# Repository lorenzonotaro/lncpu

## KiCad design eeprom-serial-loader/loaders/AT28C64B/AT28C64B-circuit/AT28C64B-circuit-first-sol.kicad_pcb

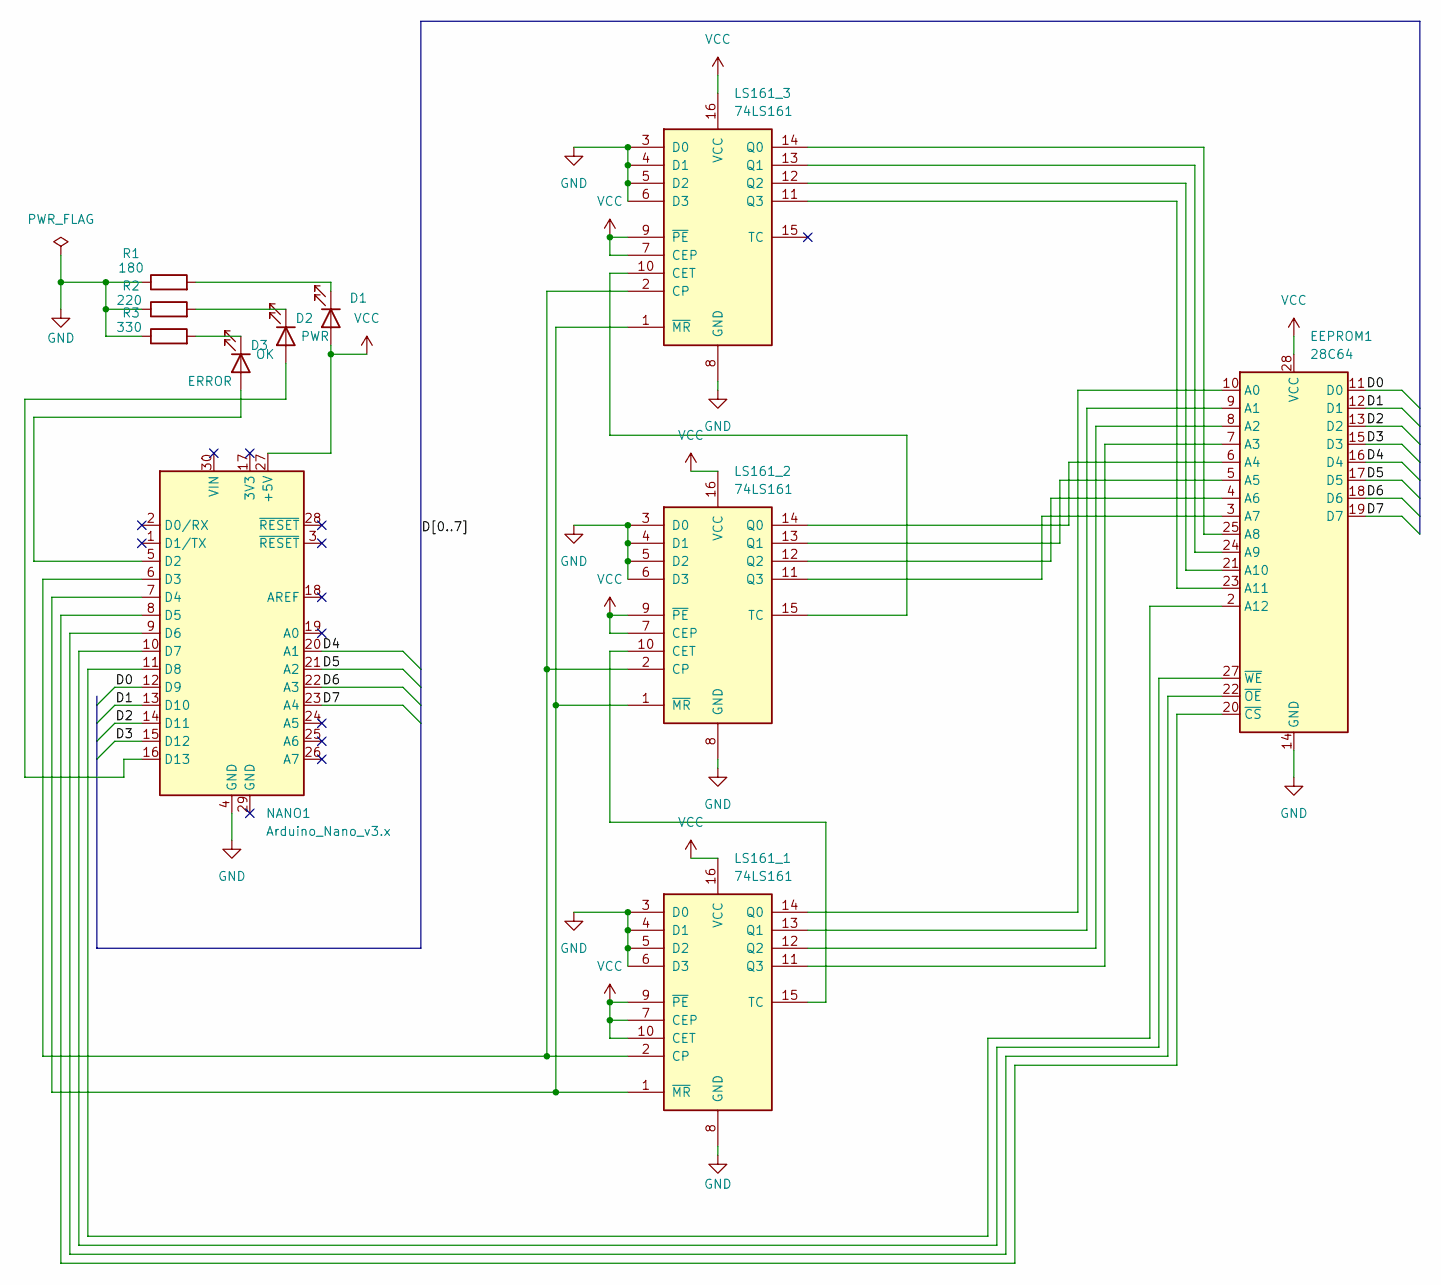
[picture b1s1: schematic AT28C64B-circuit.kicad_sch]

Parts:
D1: PWR; LED_D3.0mm
D2: OK; LED_D3.0mm
D3: ERROR; LED_D3.0mm
EEPROM1: 28C64; DIP-28_W15.24mm_Socket_LongPads
LS161_1, LS161_2, LS161_3: 74LS161; DIP-16_W7.62mm
NANO1: Arduino_Nano_v3.x; Arduino_Nano
R1: 180; R_Axial_DIN0207_L6.3mm_D2.5mm_P10.16mm_Horizontal
R2: 220; R_Axial_DIN0207_L6.3mm_D2.5mm_P10.16mm_Horizontal
R3: 330; R_Axial_DIN0207_L6.3mm_D2.5mm_P10.16mm_Horizontal

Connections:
/D0: EEPROM1.11 (D0), NANO1.12 (D9)
/D1: EEPROM1.12 (D1), NANO1.13 (D10)
/D2: EEPROM1.13 (D2), NANO1.14 (D11)
/D3: EEPROM1.15 (D3), NANO1.15 (D12)
/D4: EEPROM1.16 (D4), NANO1.20 (A1)
/D5: EEPROM1.17 (D5), NANO1.21 (A2)
/D6: EEPROM1.18 (D6), NANO1.22 (A3)
/D7: EEPROM1.19 (D7), NANO1.23 (A4)
GND: EEPROM1.14 (GND), LS161_1.3 (D0), LS161_1.4 (D1), LS161_1.5 (D2), LS161_1.6 (D3), LS161_1.8 (GND), LS161_2.3 (D0), LS161_2.4 (D1), LS161_2.5 (D2), LS161_2.6 (D3), LS161_2.8 (GND), LS161_3.3 (D0), LS161_3.4 (D1), LS161_3.5 (D2), LS161_3.6 (D3), LS161_3.8 (GND), NANO1.4 (GND), R1.1, R2.1, R3.1
unnamed: D1.1 (K), R1.2
unnamed: D2.2 (A), NANO1.16 (D13)
unnamed: D2.1 (K), R2.2
unnamed: D3.2 (A), NANO1.5 (D2)
unnamed: D3.1 (K), R3.2
unnamed: EEPROM1.10 (A0), LS161_1.14 (Q0)
unnamed: EEPROM1.9 (A1), LS161_1.13 (Q1)
unnamed: EEPROM1.8 (A2), LS161_1.12 (Q2)
unnamed: EEPROM1.7 (A3), LS161_1.11 (Q3)
unnamed: EEPROM1.6 (A4), LS161_2.14 (Q0)
unnamed: EEPROM1.5 (A5), LS161_2.13 (Q1)
unnamed: EEPROM1.4 (A6), LS161_2.12 (Q2)
unnamed: EEPROM1.3 (A7), LS161_2.11 (Q3)
unnamed: EEPROM1.25 (A8), LS161_3.14 (Q0)
unnamed: EEPROM1.24 (A9), LS161_3.13 (Q1)
unnamed: EEPROM1.21 (A10), LS161_3.12 (Q2)
unnamed: EEPROM1.23 (A11), LS161_3.11 (Q3)
unnamed: EEPROM1.2 (A12), NANO1.11 (D8)
unnamed: EEPROM1.20 (~CS), NANO1.8 (D5)
unnamed: EEPROM1.22 (~OE), NANO1.9 (D6)
unnamed: EEPROM1.27 (~WE), NANO1.10 (D7)
unnamed: LS161_1.2 (CP), LS161_2.2 (CP), LS161_3.2 (CP), NANO1.6 (D3)
unnamed: LS161_1.15 (TC), LS161_2.10 (CET)
unnamed: LS161_1.1 (~MR), LS161_2.1 (~MR), LS161_3.1 (~MR), NANO1.7 (D4)
unnamed: LS161_2.15 (TC), LS161_3.10 (CET)
VCC: D1.2 (A), EEPROM1.28 (VCC), LS161_1.7 (CEP), LS161_1.9 (~PE), LS161_1.10 (CET), LS161_1.16 (VCC), LS161_2.7 (CEP), LS161_2.9 (~PE), LS161_2.16 (VCC), LS161_3.7 (CEP), LS161_3.9 (~PE), LS161_3.16 (VCC), NANO1.27 (+5V)

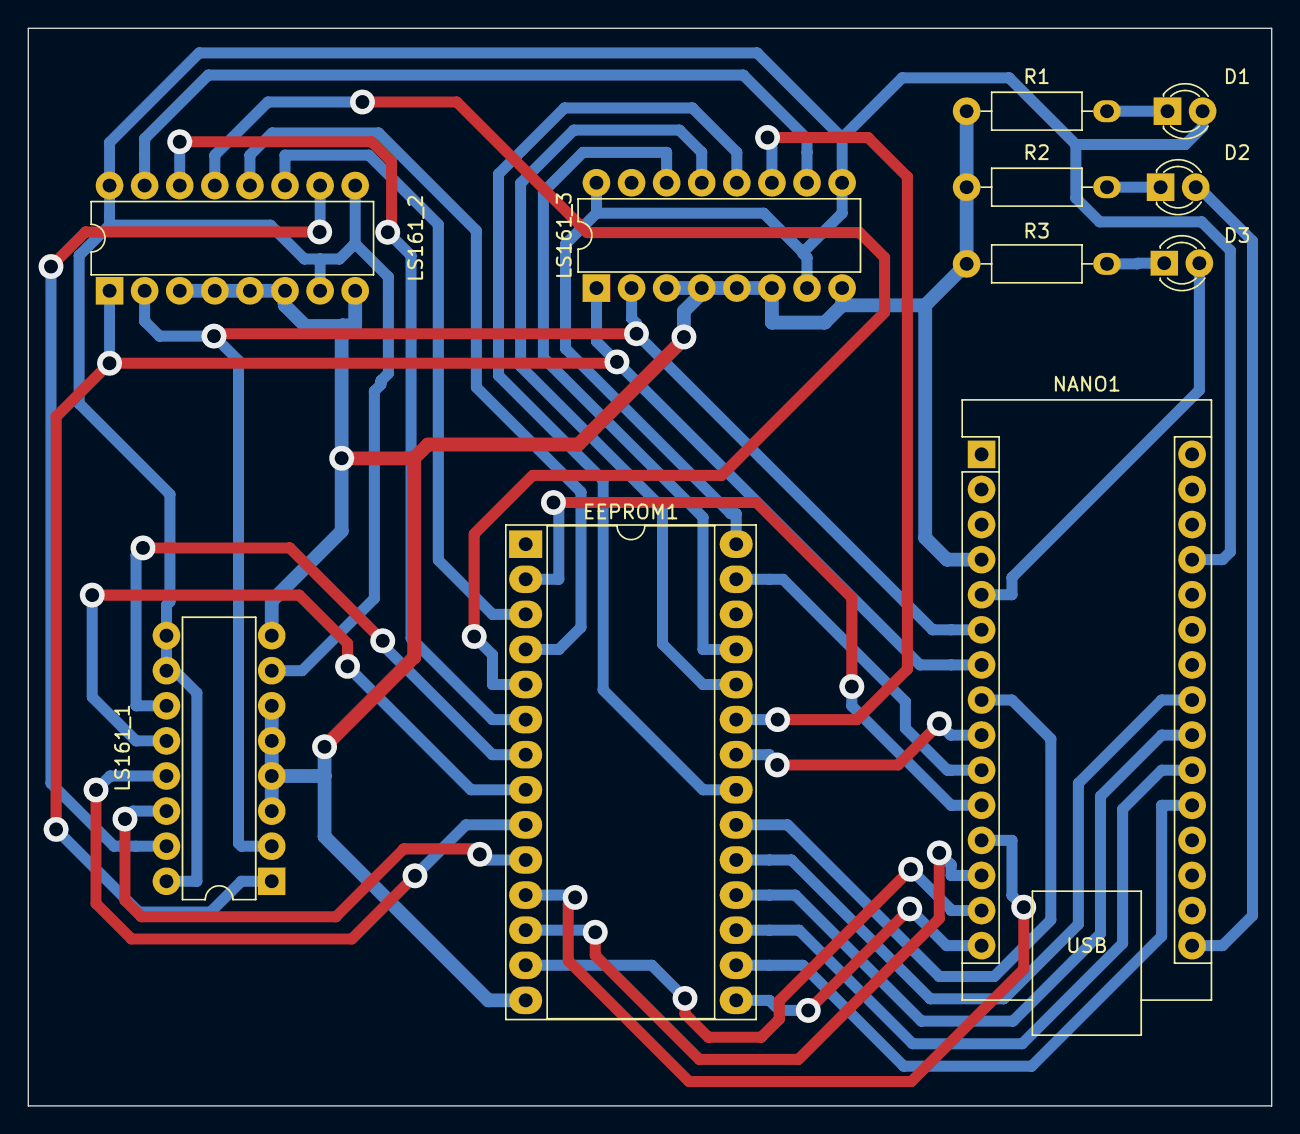
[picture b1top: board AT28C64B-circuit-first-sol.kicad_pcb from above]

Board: 2 copper layers, 90.0 x 78.0 mm, 11 parts (0 on the bottom side), 35 nets.

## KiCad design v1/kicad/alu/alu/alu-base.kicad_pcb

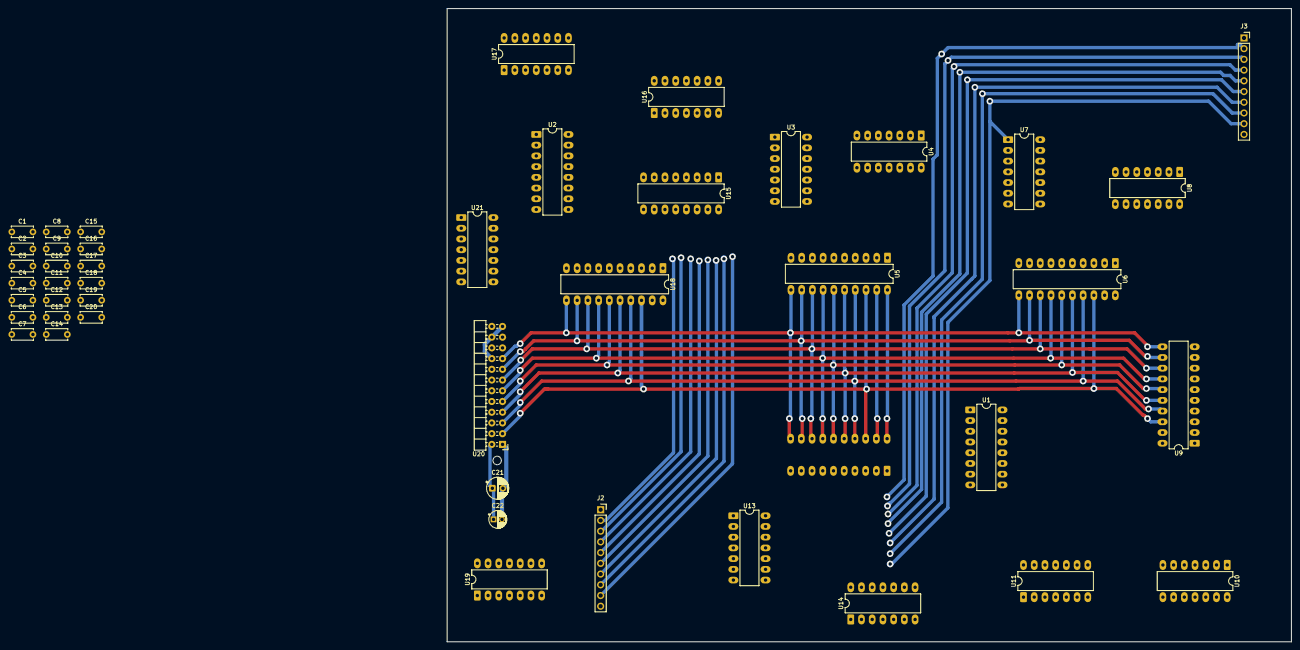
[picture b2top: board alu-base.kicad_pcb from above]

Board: 2 copper layers, 200.0 x 150.0 mm, 45 parts (1 on the bottom side), 92 nets.

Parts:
C1, C2, C3, C4, C5, C6, C7, C8, C9, C10, C11, C12, C13, C14, C15: 100n; C_Disc_D5.0mm_W2.5mm_P5.00mm
C16, C17, C18, C19, C20: 220n; C_Disc_D5.0mm_W2.5mm_P5.00mm
C21: 47uF; CP_Radial_D5.0mm_P2.50mm
C22: 1uF; CP_Radial_D4.0mm_P2.00mm-Large-Holes
J2: X_{in}; PinSocket_1x10_P2.54mm_Vertical
J3: Y_{in}; PinSocket_1x10_P2.54mm_Vertical
U1: 74LS138; DIP-16_W7.62mm_LongPads
U2, U15: 74LS283; DIP-16_W7.62mm_LongPads
U3, U4: 74LS32; DIP-14_W7.62mm_LongPads
U5, U6, U9, U12, U18: 74HCT541; DIP-20_W7.62mm_LongPads
U7, U8, U19: 74LS08; DIP-14_W7.62mm_LongPads
U10, U11, U16, U17, U21: 74LS86; DIP-14_W7.62mm_LongPads
U13, U14: 74LS04; DIP-14_W7.62mm_LongPads
U20: LNCPU Type B Header; LNCPU_Type_B_Header

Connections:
/D0: U5.18 (Y0), U6.18 (Y0), U9.18 (Y0), U12.18 (Y0), U18.18 (Y0), U20.3 (DBUS_{0})
/D1: U5.17 (Y1), U6.17 (Y1), U9.17 (Y1), U12.17 (Y1), U18.17 (Y1), U20.5 (DBUS_{1})
/D2: U5.16 (Y2), U6.16 (Y2), U9.16 (Y2), U12.16 (Y2), U18.16 (Y2), U20.7 (DBUS_{2})
/D3: U5.15 (Y3), U6.15 (Y3), U9.15 (Y3), U12.15 (Y3), U18.15 (Y3), U20.9 (DBUS_{3})
/D4: U5.14 (Y4), U6.14 (Y4), U9.14 (Y4), U12.14 (Y4), U18.14 (Y4), U20.11 (DBUS_{4})
/D5: U5.13 (Y5), U6.13 (Y5), U9.13 (Y5), U12.13 (Y5), U18.13 (Y5), U20.13 (DBUS_{5})
/D6: U5.12 (Y6), U6.12 (Y6), U9.12 (Y6), U12.12 (Y6), U18.12 (Y6), U20.15 (DBUS_{6})
/D7: U5.11 (Y7), U6.11 (Y7), U9.11 (Y7), U12.11 (Y7), U18.11 (Y7), U20.17 (DBUS_{7})
/X0: J2.2 (D0), U4.13, U8.13, U11.13, U14.3, U15.5 (A1)
/X1: J2.3 (D1), U3.13, U7.13, U10.13, U14.1, U15.3 (A2)
/X2: J2.4 (D2), U4.10, U8.10, U11.10, U13.13, U15.14 (A3)
/X3: J2.5 (D3), U3.10, U7.10, U10.10, U13.11, U15.12 (A4)
/X4: J2.6 (D4), U2.5 (A1), U4.5, U8.5, U11.5, U13.9
/X5: J2.7 (D5), U2.3 (A2), U3.5, U7.5, U10.5, U13.5
/X6: J2.8 (D6), U2.14 (A3), U4.2, U8.2, U11.2, U13.3
/X7: J2.9 (D7), U2.12 (A4), U3.2, U7.2, U10.2, U13.1
/Y0: J3.2 (D0), U4.12, U8.12, U11.12, U17.13
/Y1: J3.3 (D1), U3.12, U7.12, U10.12, U16.13
/Y2: J3.4 (D2), U4.9, U8.9, U11.9, U17.10
/Y3: J3.5 (D3), U3.9, U7.9, U10.9, U16.10
/Y4: J3.6 (D4), U4.4, U8.4, U11.4, U17.5
/Y5: J3.7 (D5), U3.4, U7.4, U10.4, U16.5
/Y6: J3.8 (D6), U4.1, U8.1, U11.1, U17.2
/Y7: J3.9 (D7), U3.1, U7.1, U10.1, U16.2
/Y_{xor}EN2_{0}: U15.6 (B1), U17.11
/Y_{xor}EN2_{1}: U15.2 (B2), U16.11
/Y_{xor}EN2_{2}: U15.15 (B3), U17.8
/Y_{xor}EN2_{3}: U15.11 (B4), U16.8
/Y_{xor}EN2_{4}: U2.6 (B1), U17.6
/Y_{xor}EN2_{5}: U2.2 (B2), U16.6
/Y_{xor}EN2_{6}: U2.15 (B3), U17.3
/Y_{xor}EN2_{7}: U2.11 (B4), U16.3
/~EN1: U1.14 (O1), U19.5
/~EN2: U1.13 (O2), U14.5, U19.4
/~EN3: U1.12 (O3), U5.1 (G1)
/~EN4: U1.11 (O4), U6.1 (G1)
/~EN5: U1.10 (O5), U9.1 (G1)
/~EN6: U1.9 (O6), U12.1 (G1)
C_{out}: U19.3, U20.14 (CTRL_{5})
GND: C1.2, C2.1, C3.1, C4.1, C5.1, C6.1, C7.1, C8.1, C9.1, C10.1, C11.1, C12.1, C13.1, C14.2, C15.2, C16.2, C17.2, C18.2, C19.2, C20.2, C21.2, C22.2, J2.1 (GND), J2.10 (GND), J3.1 (GND), J3.10 (GND), U1.8 (GND), U2.8 (GND), U3.7 (GND), U4.7 (GND), U5.10 (GND), U6.10 (GND), U7.7 (GND), U8.7 (GND), U9.10 (GND), U10.7 (GND), U11.7 (GND), U12.10 (GND), U13.7 (GND), U14.7 (GND), U14.11, U14.13, U15.8 (GND), U16.7 (GND), U17.7 (GND), U18.10 (GND), U19.7 (GND), U19.9, U19.10, U19.12, U19.13, U20.1 (GND), U20.18 (GND), U20.22 (GND), U20.23 (GND), U21.4, U21.5, U21.7 (GND), U21.9, U21.10, U21.12, U21.13
unnamed: U1.1 (A0), U20.12 (CTRL_{4})
unnamed: U1.2 (A1), U20.10 (CTRL_{3})
unnamed: U1.3 (A2), U20.8 (CTRL_{2})
unnamed: U1.4 (E1), U20.4 (CTRL_{0})
unnamed: U2.9 (C4), U21.2
unnamed: U4.11, U5.2 (A0)
unnamed: U3.11, U5.3 (A1)
unnamed: U4.8, U5.4 (A2)
unnamed: U3.8, U5.5 (A3)
unnamed: U4.6, U5.6 (A4)
unnamed: U3.6, U5.7 (A5)
unnamed: U4.3, U5.8 (A6)
unnamed: U3.3, U5.9 (A7)
unnamed: U6.2 (A0), U8.11
unnamed: U6.3 (A1), U7.11
unnamed: U6.4 (A2), U8.8
unnamed: U6.5 (A3), U7.8
unnamed: U6.6 (A4), U8.6
unnamed: U6.7 (A5), U7.6
unnamed: U6.8 (A6), U8.3
unnamed: U6.9 (A7), U7.3
unnamed: U9.2 (A0), U11.11
unnamed: U9.3 (A1), U10.11
unnamed: U9.4 (A2), U11.8
unnamed: U9.5 (A3), U10.8
unnamed: U9.6 (A4), U11.6
unnamed: U9.7 (A5), U10.6
unnamed: U9.8 (A6), U11.3
unnamed: U9.9 (A7), U10.3
unnamed: U12.2 (A0), U14.4
unnamed: U12.3 (A1), U14.2
unnamed: U12.4 (A2), U13.12
unnamed: U12.5 (A3), U13.10
unnamed: U12.6 (A4), U13.8
unnamed: U12.7 (A5), U13.6
unnamed: U12.8 (A6), U13.4
unnamed: U12.9 (A7), U13.2
unnamed: U14.8, U19.2
unnamed: U14.6, U15.7 (C0), U16.1, U16.4, U16.9, U16.12, U17.1, U17.4, U17.9, U17.12, U21.1
unnamed: U2.7 (C0), U15.9 (C4)
unnamed: U15.4 (S1), U18.2 (A0)
unnamed: U15.1 (S2), U18.3 (A1)
unnamed: U15.13 (S3), U18.4 (A2)
unnamed: U15.10 (S4), U18.5 (A3)
unnamed: U2.4 (S1), U18.6 (A4)
unnamed: U2.1 (S2), U18.7 (A5)
unnamed: U2.13 (S3), U18.8 (A6)
unnamed: U2.10 (S4), U18.9 (A7)
unnamed: U14.9, U18.1 (G1), U19.6
unnamed: U19.1, U21.3
VCC: C1.1, C2.2, C3.2, C4.2, C5.2, C6.2, C7.2, C8.2, C9.2, C10.2, C11.2, C12.2, C13.2, C14.1, C15.1, C16.1, C17.1, C18.1, C19.1, C20.1, C21.1, C22.1, U1.6 (E3), U1.16 (VCC), U2.16 (VCC), U3.14 (VCC), U4.14 (VCC), U5.20 (VCC), U6.20 (VCC), U7.14 (VCC), U8.14 (VCC), U9.20 (VCC), U10.14 (VCC), U11.14 (VCC), U12.20 (VCC), U13.14 (VCC), U14.14 (VCC), U15.16 (VCC), U16.14 (VCC), U17.14 (VCC), U18.20 (VCC), U19.14 (VCC), U20.2 (VCC), U20.24 (VCC), U21.14 (VCC)
~ALU_{out}: U1.5 (E2), U5.19 (G2), U6.19 (G2), U9.19 (G2), U12.19 (G2), U18.19 (G2), U20.6 (CTRL_{1})

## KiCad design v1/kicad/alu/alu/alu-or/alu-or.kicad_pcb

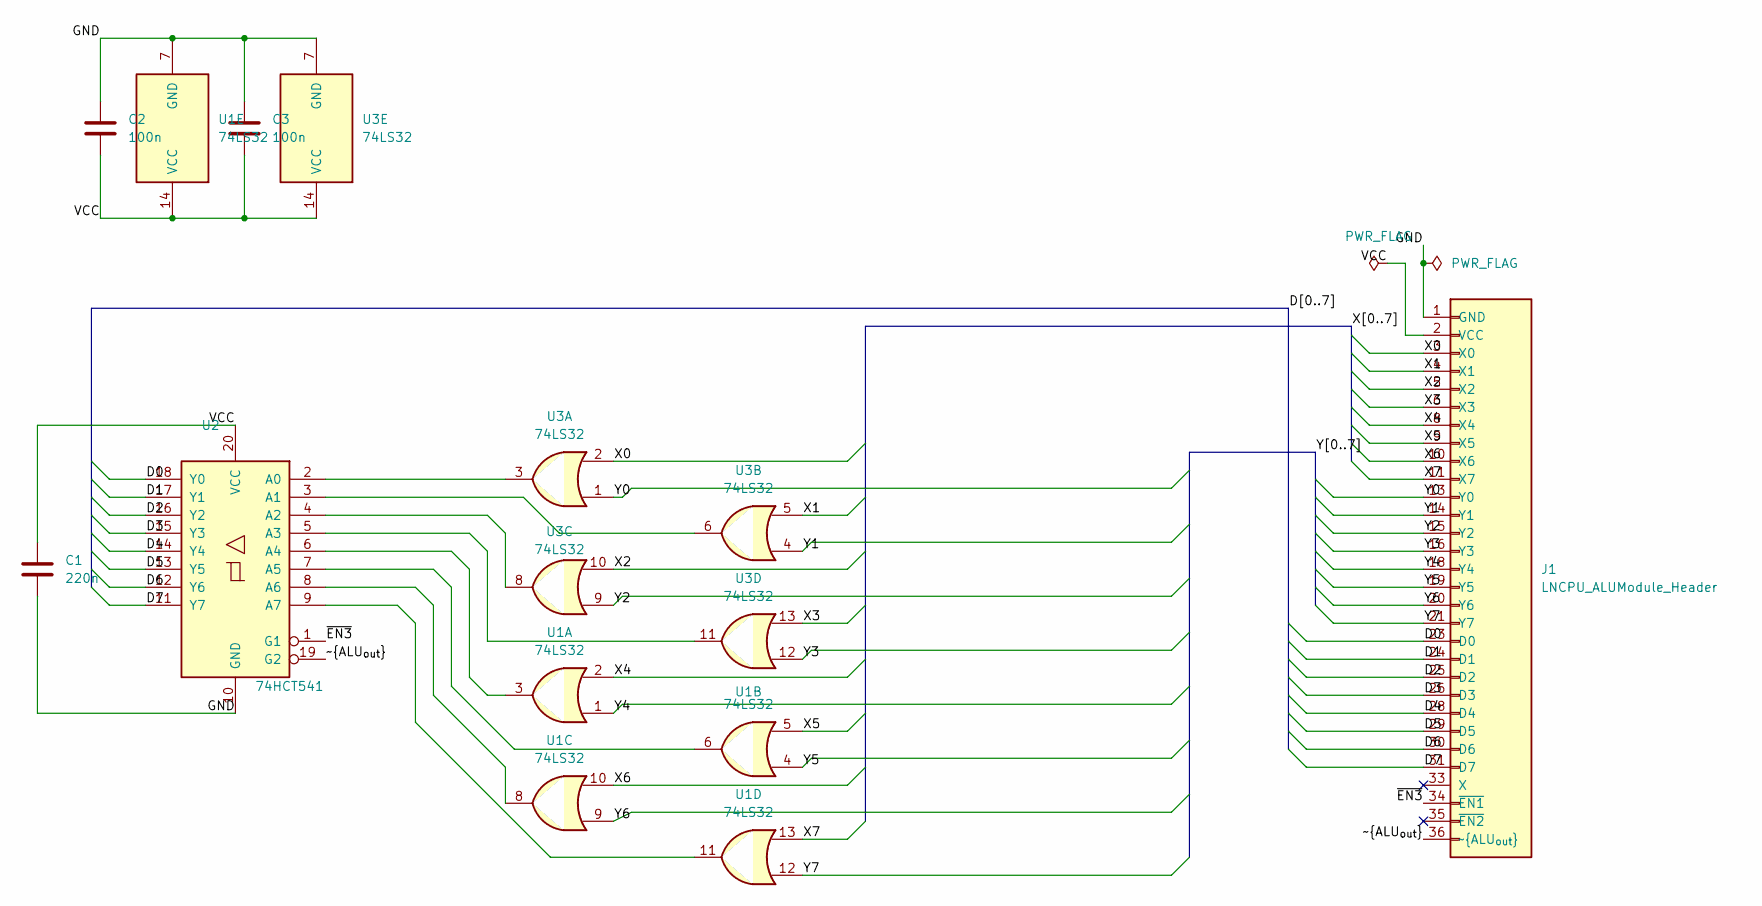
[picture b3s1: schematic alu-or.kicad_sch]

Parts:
C1: 220n; C_Disc_D5.0mm_W2.5mm_P5.00mm
C2, C3: 100n; C_Disc_D5.0mm_W2.5mm_P5.00mm
J1: LNCPU_ALUModule_Header; LNCPU_ALU_Module_Header
U1, U3: 74LS32; DIP-14_W7.62mm_LongPads
U2: 74HCT541; DIP-20_W7.62mm_LongPads

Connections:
/D0: J1.23 (D0), U2.18 (Y0)
/D1: J1.24 (D1), U2.17 (Y1)
/D2: J1.25 (D2), U2.16 (Y2)
/D3: J1.26 (D3), U2.15 (Y3)
/D4: J1.28 (D4), U2.14 (Y4)
/D5: J1.29 (D5), U2.13 (Y5)
/D6: J1.30 (D6), U2.12 (Y6)
/D7: J1.31 (D7), U2.11 (Y7)
/GND: C1.2, C2.1, C3.1, J1.1 (GND), J1.7 (GND), J1.12 (GND), J1.17 (GND), J1.22 (GND), J1.27 (GND), J1.32 (GND), J1.37 (GND), U1.7 (GND), U2.10 (GND), U3.7 (GND)
/VCC: C1.1, C2.2, C3.2, J1.2 (VCC), J1.38 (VCC), U1.14 (VCC), U2.20 (VCC), U3.14 (VCC)
/X0: J1.3 (X0), U3.2
/X1: J1.4 (X1), U3.5
/X2: J1.5 (X2), U3.10
/X3: J1.6 (X3), U3.13
/X4: J1.8 (X4), U1.2
/X5: J1.9 (X5), U1.5
/X6: J1.10 (X6), U1.10
/X7: J1.11 (X7), U1.13
/Y0: J1.13 (Y0), U3.1
/Y1: J1.14 (Y1), U3.4
/Y2: J1.15 (Y2), U3.9
/Y3: J1.16 (Y3), U3.12
/Y4: J1.18 (Y4), U1.1
/Y5: J1.19 (Y5), U1.4
/Y6: J1.20 (Y6), U1.9
/Y7: J1.21 (Y7), U1.12
/~ALU_{out}: J1.36 (~ALU_{out}), U2.19 (G2)
/~EN3: J1.34 (~EN1), U2.1 (G1)
unnamed: U2.2 (A0), U3.3
unnamed: U2.3 (A1), U3.6
unnamed: U2.4 (A2), U3.8
unnamed: U2.5 (A3), U3.11
unnamed: U1.3, U2.6 (A4)
unnamed: U1.6, U2.7 (A5)
unnamed: U1.8, U2.8 (A6)
unnamed: U1.11, U2.9 (A7)

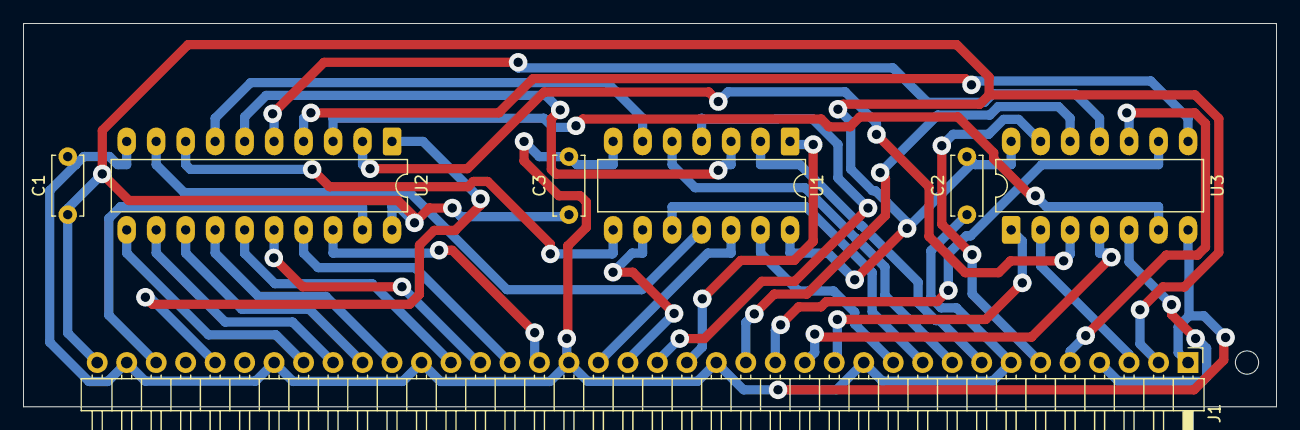
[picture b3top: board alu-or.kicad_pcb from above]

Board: 2 copper layers, 107.9 x 33.0 mm, 7 parts (0 on the bottom side), 36 nets.

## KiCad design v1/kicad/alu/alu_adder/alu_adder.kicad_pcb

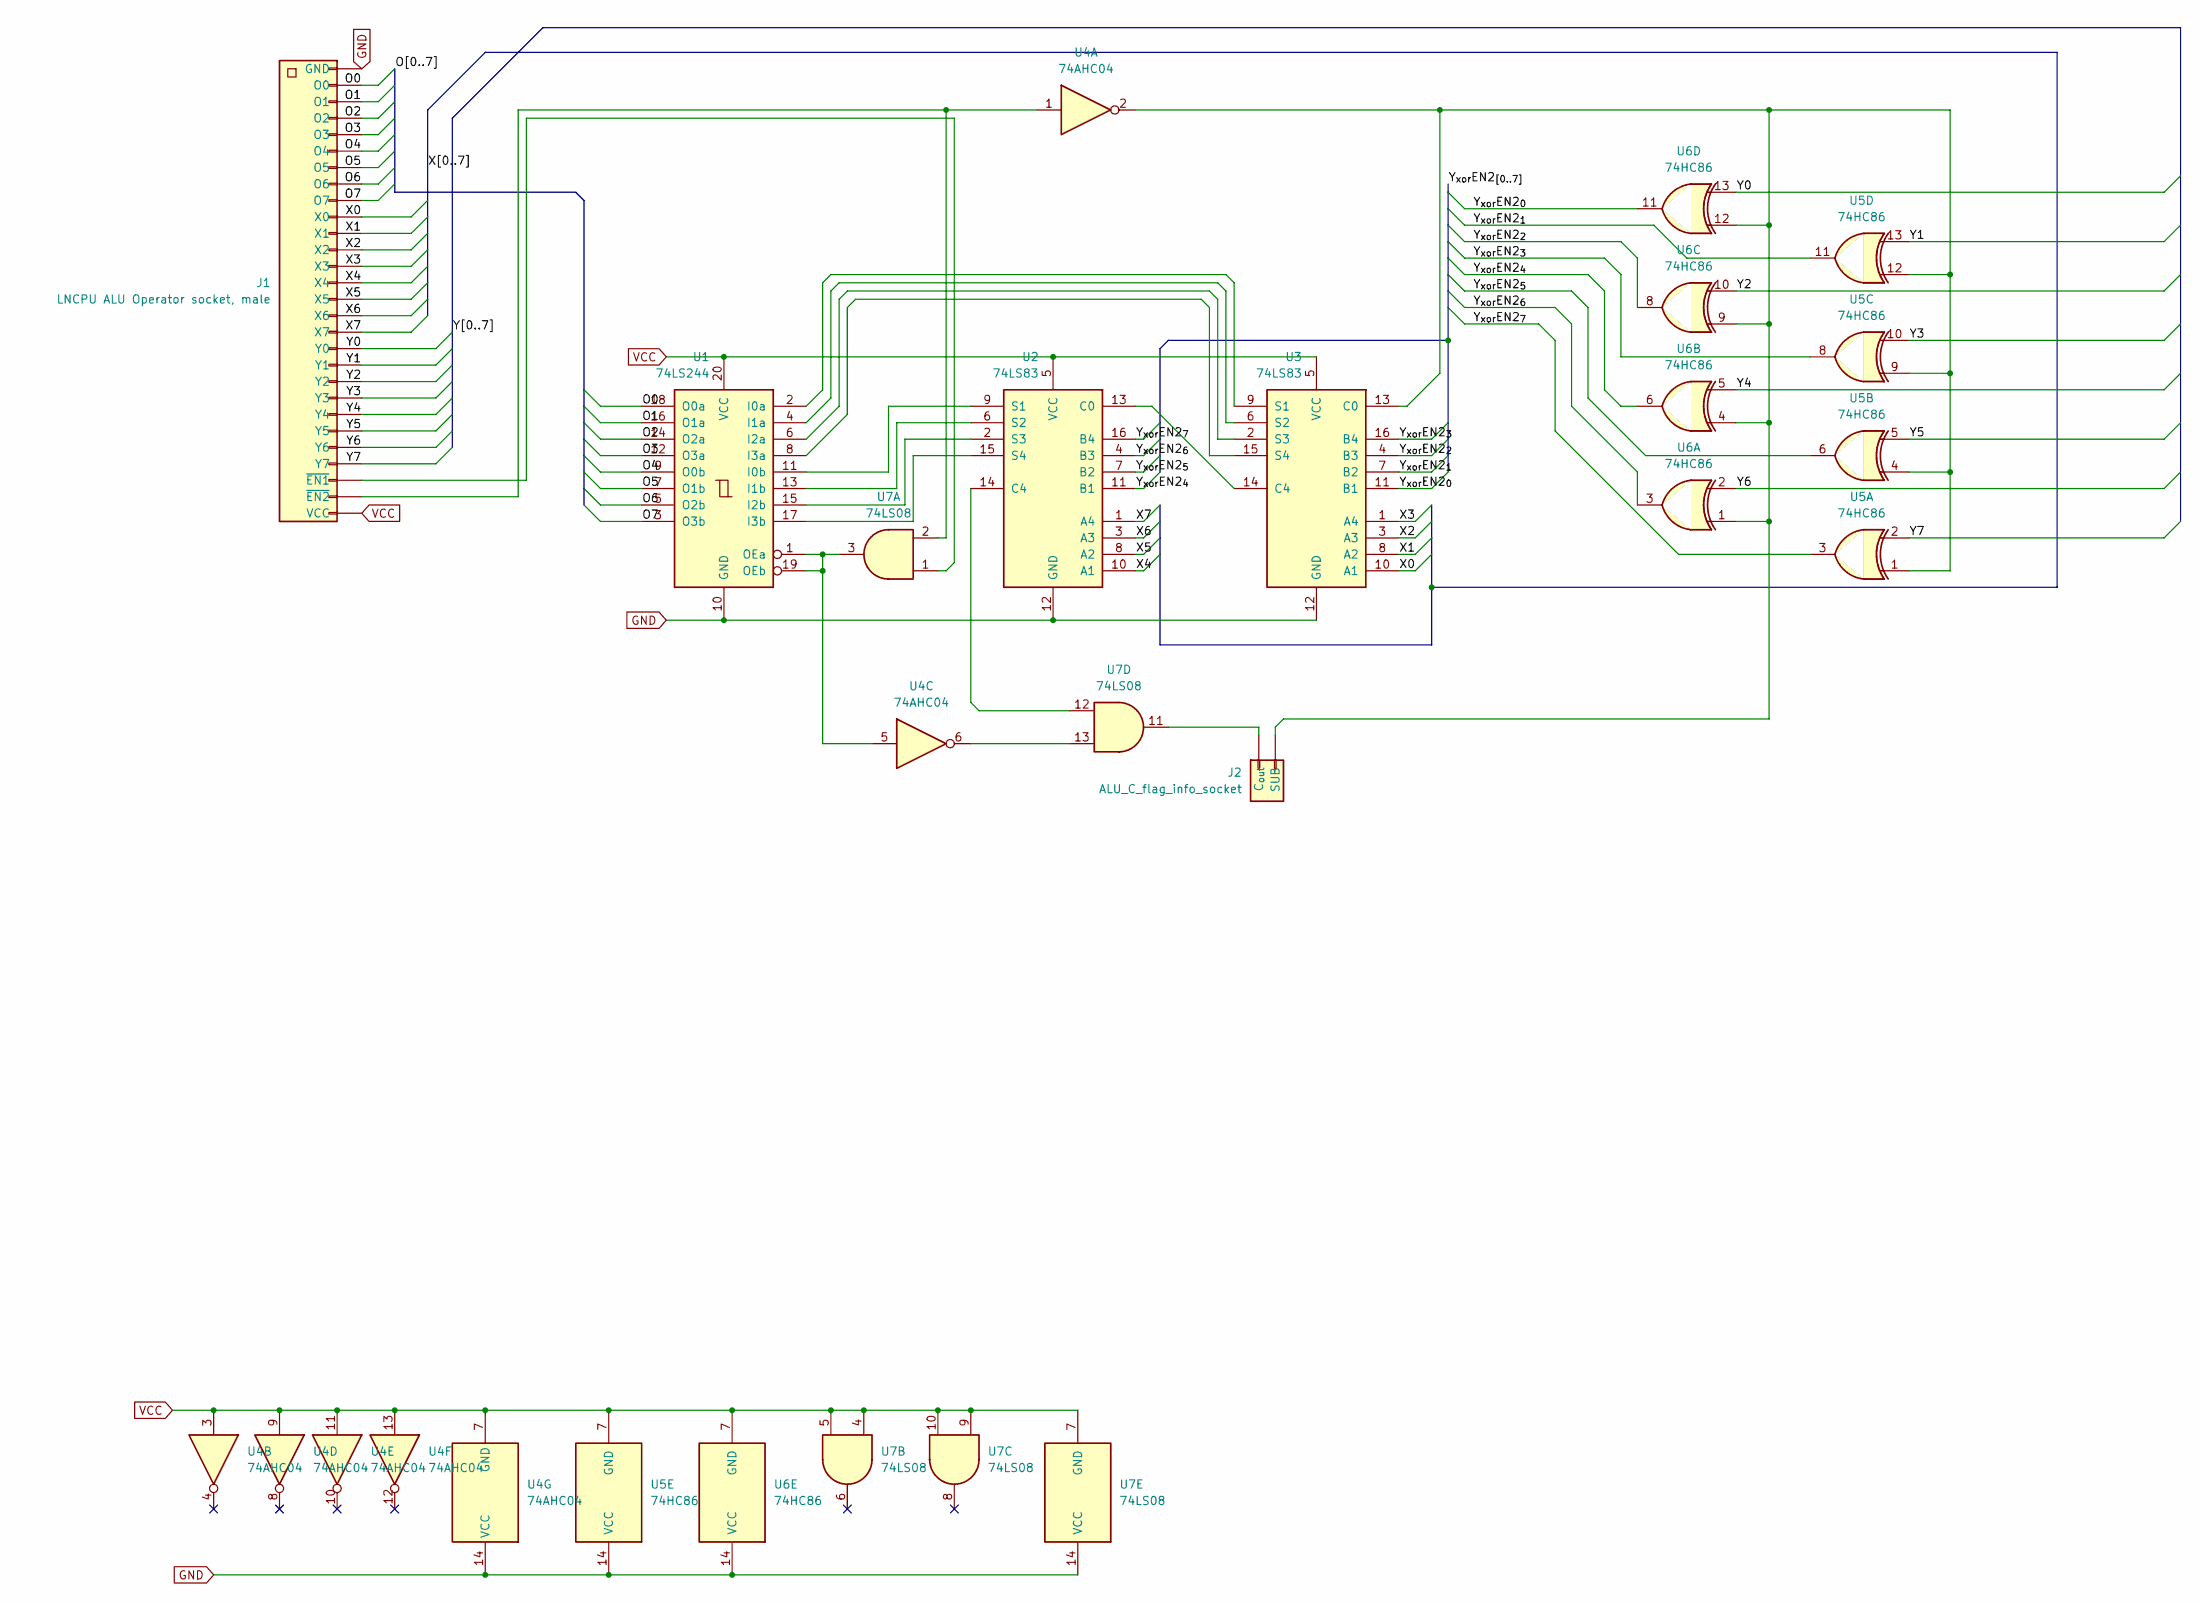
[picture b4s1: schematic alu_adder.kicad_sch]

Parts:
J1: LNCPU ALU Operator socket, male; PinHeader_1x28_P2.54mm_Horizontal
J2: ALU_C_flag_info_socket; PinSocket_1x02_P2.54mm_Vertical
U1: 74LS244; DIP-20_W7.62mm
U2, U3: 74LS83; DIP-16_W7.62mm
U4: 74AHC04; DIP-14_W7.62mm
U5, U6: 74HC86; DIP-14_W7.62mm
U7: 74LS08; DIP-14_W7.62mm

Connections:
/O0: J1.2 (O0), U1.18 (O0a)
/O1: J1.3 (O1), U1.16 (O1a)
/O2: J1.4 (O2), U1.14 (O2a)
/O3: J1.5 (O3), U1.12 (O3a)
/O4: J1.6 (O4), U1.9 (O0b)
/O5: J1.7 (O5), U1.7 (O1b)
/O6: J1.8 (O6), U1.5 (O2b)
/O7: J1.9 (O7), U1.3 (O3b)
/X0: J1.10 (X0), U3.10 (A1)
/X1: J1.11 (X1), U3.8 (A2)
/X2: J1.12 (X2), U3.3 (A3)
/X3: J1.13 (X3), U3.1 (A4)
/X4: J1.14 (X4), U2.10 (A1)
/X5: J1.15 (X5), U2.8 (A2)
/X6: J1.16 (X6), U2.3 (A3)
/X7: J1.17 (X7), U2.1 (A4)
/Y0: J1.18 (Y0), U6.13
/Y1: J1.19 (Y1), U5.13
/Y2: J1.20 (Y2), U6.10
/Y3: J1.21 (Y3), U5.10
/Y4: J1.22 (Y4), U6.5
/Y5: J1.23 (Y5), U5.5
/Y6: J1.24 (Y6), U6.2
/Y7: J1.25 (Y7), U5.2
/Y_{xor}EN2_{0}: U3.11 (B1), U6.11
/Y_{xor}EN2_{1}: U3.7 (B2), U5.11
/Y_{xor}EN2_{2}: U3.4 (B3), U6.8
/Y_{xor}EN2_{3}: U3.16 (B4), U5.8
/Y_{xor}EN2_{4}: U2.11 (B1), U6.6
/Y_{xor}EN2_{5}: U2.7 (B2), U5.6
/Y_{xor}EN2_{6}: U2.4 (B3), U6.3
/Y_{xor}EN2_{7}: U2.16 (B4), U5.3
GND: J1.1 (GND), U1.10 (GND), U2.12 (GND), U3.12 (GND), U4.14 (VCC), U5.14 (VCC), U6.14 (VCC), U7.14 (VCC)
unnamed: J1.26 (~EN1), U7.1
unnamed: J1.27 (~EN2), U4.1, U7.2
unnamed: J2.1 (C_{out}), U7.11
unnamed: J2.2 (SUB), U3.13 (C0), U4.2, U5.1, U5.4, U5.9, U5.12, U6.1, U6.4, U6.9, U6.12
unnamed: U1.2 (I0a), U3.9 (S1)
unnamed: U1.11 (I0b), U2.9 (S1)
unnamed: U1.4 (I1a), U3.6 (S2)
unnamed: U1.13 (I1b), U2.6 (S2)
unnamed: U1.6 (I2a), U3.2 (S3)
unnamed: U1.15 (I2b), U2.2 (S3)
unnamed: U1.8 (I3a), U3.15 (S4)
unnamed: U1.17 (I3b), U2.15 (S4)
unnamed: U1.1 (OEa), U1.19 (OEb), U4.5, U7.3
unnamed: U2.13 (C0), U3.14 (C4)
unnamed: U2.14 (C4), U7.12
unnamed: U4.6, U7.13
VCC: J1.28 (VCC), U1.20 (VCC), U2.5 (VCC), U3.5 (VCC), U4.3, U4.7 (GND), U4.9, U4.11, U4.13, U5.7 (GND), U6.7 (GND), U7.4, U7.5, U7.7 (GND), U7.9, U7.10

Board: 2 copper layers, 9 parts (0 on the bottom side), 50 nets, no tracks yet.

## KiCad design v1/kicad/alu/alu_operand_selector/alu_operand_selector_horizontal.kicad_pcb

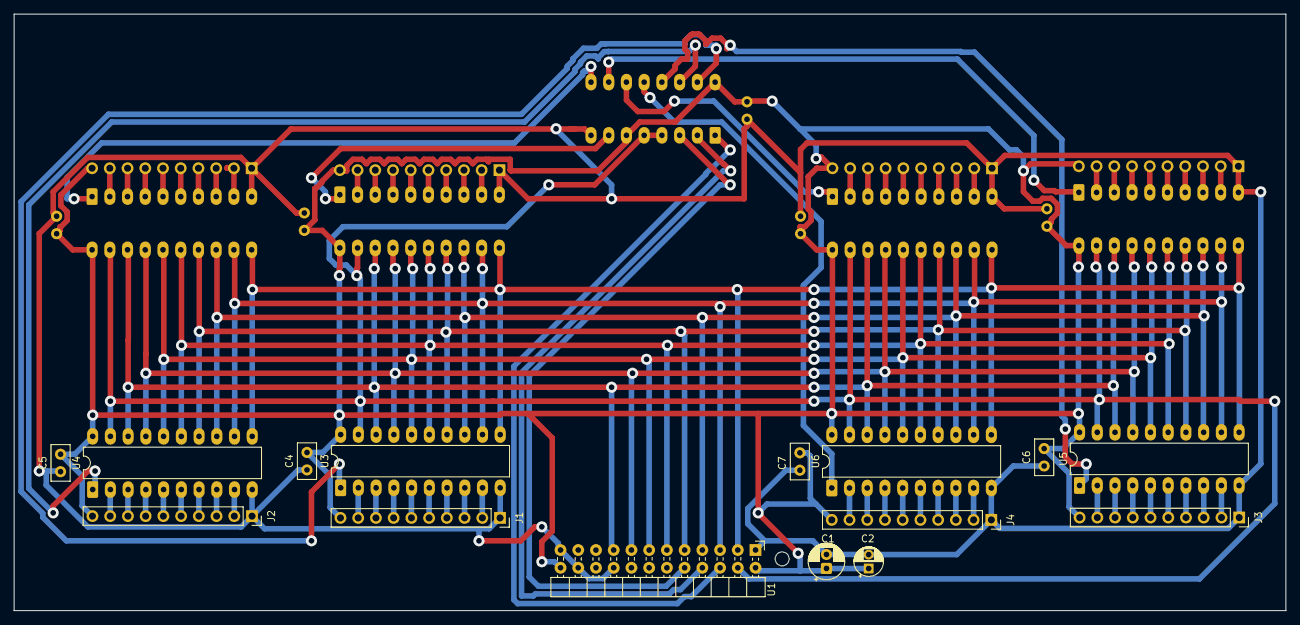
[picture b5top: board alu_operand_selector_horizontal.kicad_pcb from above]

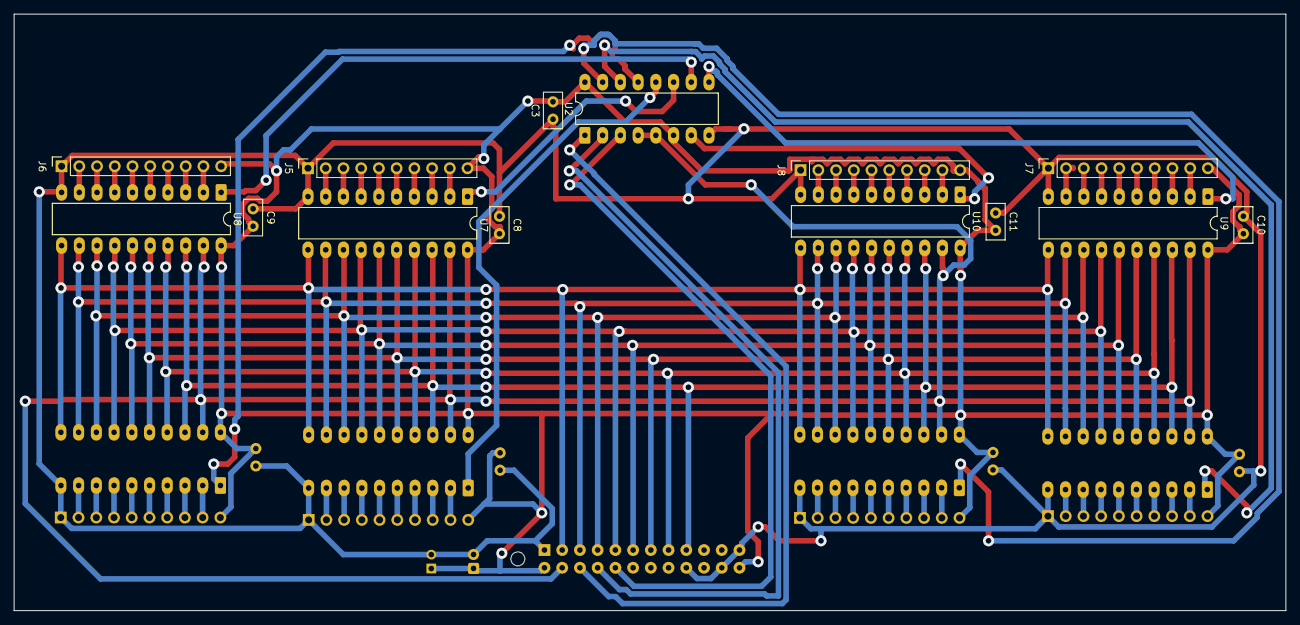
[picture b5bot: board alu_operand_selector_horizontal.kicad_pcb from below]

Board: 2 copper layers, 182.2 x 85.5 mm, 29 parts (14 on the bottom side), 86 nets.

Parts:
C1: 47u; CP_Radial_D5.0mm_P2.00mm
C2: 1u; CP_Radial_D4.0mm_P2.00mm-Large-Holes
C3: 100n; C_Disc_D5.0mm_W2.5mm_P2.50mm
C4, C5, C6, C7, C8, C9, C10, C11: 220n; C_Disc_D5.0mm_W2.5mm_P2.50mm
J1: A_{in}; PinSocket_1x10_P2.54mm_Vertical
J2: B_{in}; PinSocket_1x10_P2.54mm_Vertical
J3: C_{in}; PinSocket_1x10_P2.54mm_Vertical
J4: D_{in}; PinSocket_1x10_P2.54mm_Vertical
J5: E_{in}; PinSocket_1x10_P2.54mm_Vertical
J6: F_{in}; PinSocket_1x10_P2.54mm_Vertical
J7: G_{in}; PinSocket_1x10_P2.54mm_Vertical
J8: H_{in}; PinSocket_1x10_P2.54mm_Vertical
U1: LNCPU Type B Header; LNCPU_Type_B_Header
U2: 74HC138; DIP-16_W7.62mm_LongPads
U3, U4, U5, U6, U7, U8, U9, U10: 74HCT541; DIP-20_W7.62mm_LongPads

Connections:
/EN.A: U2.15 (Y0), U3.1 (G1)
/EN.B: U2.14 (Y1), U4.1 (G1)
/EN.C: U2.13 (Y2), U5.1 (G1)
/EN.D: U2.12 (Y3), U6.1 (G1)
/EN.E: U2.11 (Y4), U7.1 (G1)
/EN.F: U2.10 (Y5), U8.1 (G1)
/EN.G: U2.9 (Y6), U9.1 (G1)
/EN.H: U2.7 (Y7), U10.1 (G1)
/OP_{out}0: U1.17 (DBUS_{7}), U3.18 (Y0), U4.18 (Y0), U5.18 (Y0), U6.18 (Y0), U7.18 (Y0), U8.18 (Y0), U9.18 (Y0), U10.18 (Y0)
/OP_{out}1: U1.15 (DBUS_{6}), U3.17 (Y1), U4.17 (Y1), U5.17 (Y1), U6.17 (Y1), U7.17 (Y1), U8.17 (Y1), U9.17 (Y1), U10.17 (Y1)
/OP_{out}2: U1.13 (DBUS_{5}), U3.16 (Y2), U4.16 (Y2), U5.16 (Y2), U6.16 (Y2), U7.16 (Y2), U8.16 (Y2), U9.16 (Y2), U10.16 (Y2)
/OP_{out}3: U1.11 (DBUS_{4}), U3.15 (Y3), U4.15 (Y3), U5.15 (Y3), U6.15 (Y3), U7.15 (Y3), U8.15 (Y3), U9.15 (Y3), U10.15 (Y3)
/OP_{out}4: U1.9 (DBUS_{3}), U3.14 (Y4), U4.14 (Y4), U5.14 (Y4), U6.14 (Y4), U7.14 (Y4), U8.14 (Y4), U9.14 (Y4), U10.14 (Y4)
/OP_{out}5: U1.7 (DBUS_{2}), U3.13 (Y5), U4.13 (Y5), U5.13 (Y5), U6.13 (Y5), U7.13 (Y5), U8.13 (Y5), U9.13 (Y5), U10.13 (Y5)
/OP_{out}6: U1.5 (DBUS_{1}), U3.12 (Y6), U4.12 (Y6), U5.12 (Y6), U6.12 (Y6), U7.12 (Y6), U8.12 (Y6), U9.12 (Y6), U10.12 (Y6)
/OP_{out}7: U1.3 (DBUS_{0}), U3.11 (Y7), U4.11 (Y7), U5.11 (Y7), U6.11 (Y7), U7.11 (Y7), U8.11 (Y7), U9.11 (Y7), U10.11 (Y7)
/~EN: U1.4 (CTRL_{0}), U2.4 (~E1), U2.5 (~E2), U3.19 (G2), U4.19 (G2), U5.19 (G2), U6.19 (G2), U7.19 (G2), U8.19 (G2), U9.19 (G2), U10.19 (G2)
unnamed: J1.2 (D0), U3.9 (A7)
unnamed: J1.3 (D1), U3.8 (A6)
unnamed: J1.4 (D2), U3.7 (A5)
unnamed: J1.5 (D3), U3.6 (A4)
unnamed: J1.6 (D4), U3.5 (A3)
unnamed: J1.7 (D5), U3.4 (A2)
unnamed: J1.8 (D6), U3.3 (A1)
unnamed: J1.9 (D7), U3.2 (A0)
unnamed: C1.2, C2.2, C3.2, C4.2, C5.2, C6.2, C7.2, C8.2, C9.2, C10.2, C11.2, J1.1 (GND), J2.1 (GND), J3.1 (GND), J4.1 (GND), J5.1 (GND), J6.1 (GND), J7.1 (GND), J8.1 (GND), U1.1 (GND), U1.18 (GND), U1.22 (GND), U1.23 (GND), U2.8 (GND), U3.10 (GND), U4.10 (GND), U5.10 (GND), U6.10 (GND), U7.10 (GND), U8.10 (GND), U9.10 (GND), U10.10 (GND)
unnamed: C1.1, C2.1, C3.1, C4.1, C5.1, C6.1, C7.1, C8.1, C9.1, C10.1, C11.1, J1.10 (VCC), J2.10 (VCC), J3.10 (VCC), J4.10 (VCC), J5.10 (VCC), J6.10 (VCC), J7.10 (VCC), J8.10 (VCC), U1.2 (VCC), U1.24 (VCC), U2.6 (E3), U2.16 (VCC), U3.20 (VCC), U4.20 (VCC), U5.20 (VCC), U6.20 (VCC), U7.20 (VCC), U8.20 (VCC), U9.20 (VCC), U10.20 (VCC)
unnamed: J2.2 (D0), U4.9 (A7)
unnamed: J2.3 (D1), U4.8 (A6)
unnamed: J2.4 (D2), U4.7 (A5)
unnamed: J2.5 (D3), U4.6 (A4)
unnamed: J2.6 (D4), U4.5 (A3)
unnamed: J2.7 (D5), U4.4 (A2)
unnamed: J2.8 (D6), U4.3 (A1)
unnamed: J2.9 (D7), U4.2 (A0)
unnamed: J3.2 (D0), U5.9 (A7)
unnamed: J3.3 (D1), U5.8 (A6)
unnamed: J3.4 (D2), U5.7 (A5)
unnamed: J3.5 (D3), U5.6 (A4)
unnamed: J3.6 (D4), U5.5 (A3)
unnamed: J3.7 (D5), U5.4 (A2)
unnamed: J3.8 (D6), U5.3 (A1)
unnamed: J3.9 (D7), U5.2 (A0)
unnamed: J4.2 (D0), U6.9 (A7)
unnamed: J4.3 (D1), U6.8 (A6)
unnamed: J4.4 (D2), U6.7 (A5)
unnamed: J4.5 (D3), U6.6 (A4)
unnamed: J4.6 (D4), U6.5 (A3)
unnamed: J4.7 (D5), U6.4 (A2)
unnamed: J4.8 (D6), U6.3 (A1)
unnamed: J4.9 (D7), U6.2 (A0)
unnamed: J5.2 (D0), U7.9 (A7)
unnamed: J5.3 (D1), U7.8 (A6)
unnamed: J5.4 (D2), U7.7 (A5)
unnamed: J5.5 (D3), U7.6 (A4)
unnamed: J5.6 (D4), U7.5 (A3)
unnamed: J5.7 (D5), U7.4 (A2)
unnamed: J5.8 (D6), U7.3 (A1)
unnamed: J5.9 (D7), U7.2 (A0)
unnamed: J6.2 (D0), U8.9 (A7)
unnamed: J6.3 (D1), U8.8 (A6)
unnamed: J6.4 (D2), U8.7 (A5)
unnamed: J6.5 (D3), U8.6 (A4)
unnamed: J6.6 (D4), U8.5 (A3)
unnamed: J6.7 (D5), U8.4 (A2)
unnamed: J6.8 (D6), U8.3 (A1)
unnamed: J6.9 (D7), U8.2 (A0)
unnamed: J7.2 (D0), U9.9 (A7)
unnamed: J7.3 (D1), U9.8 (A6)
unnamed: J7.4 (D2), U9.7 (A5)
unnamed: J7.5 (D3), U9.6 (A4)
unnamed: J7.6 (D4), U9.5 (A3)
unnamed: J7.7 (D5), U9.4 (A2)
unnamed: J7.8 (D6), U9.3 (A1)
unnamed: J7.9 (D7), U9.2 (A0)
unnamed: J8.2 (D0), U10.9 (A7)
unnamed: J8.3 (D1), U10.8 (A6)
unnamed: J8.4 (D2), U10.7 (A5)
unnamed: J8.5 (D3), U10.6 (A4)
unnamed: J8.6 (D4), U10.5 (A3)
unnamed: J8.7 (D5), U10.4 (A2)
unnamed: J8.8 (D6), U10.3 (A1)
unnamed: J8.9 (D7), U10.2 (A0)
unnamed: U1.6 (CTRL_{1}), U2.1 (A0)
unnamed: U1.8 (CTRL_{2}), U2.2 (A1)
unnamed: U1.10 (CTRL_{3}), U2.3 (A2)
